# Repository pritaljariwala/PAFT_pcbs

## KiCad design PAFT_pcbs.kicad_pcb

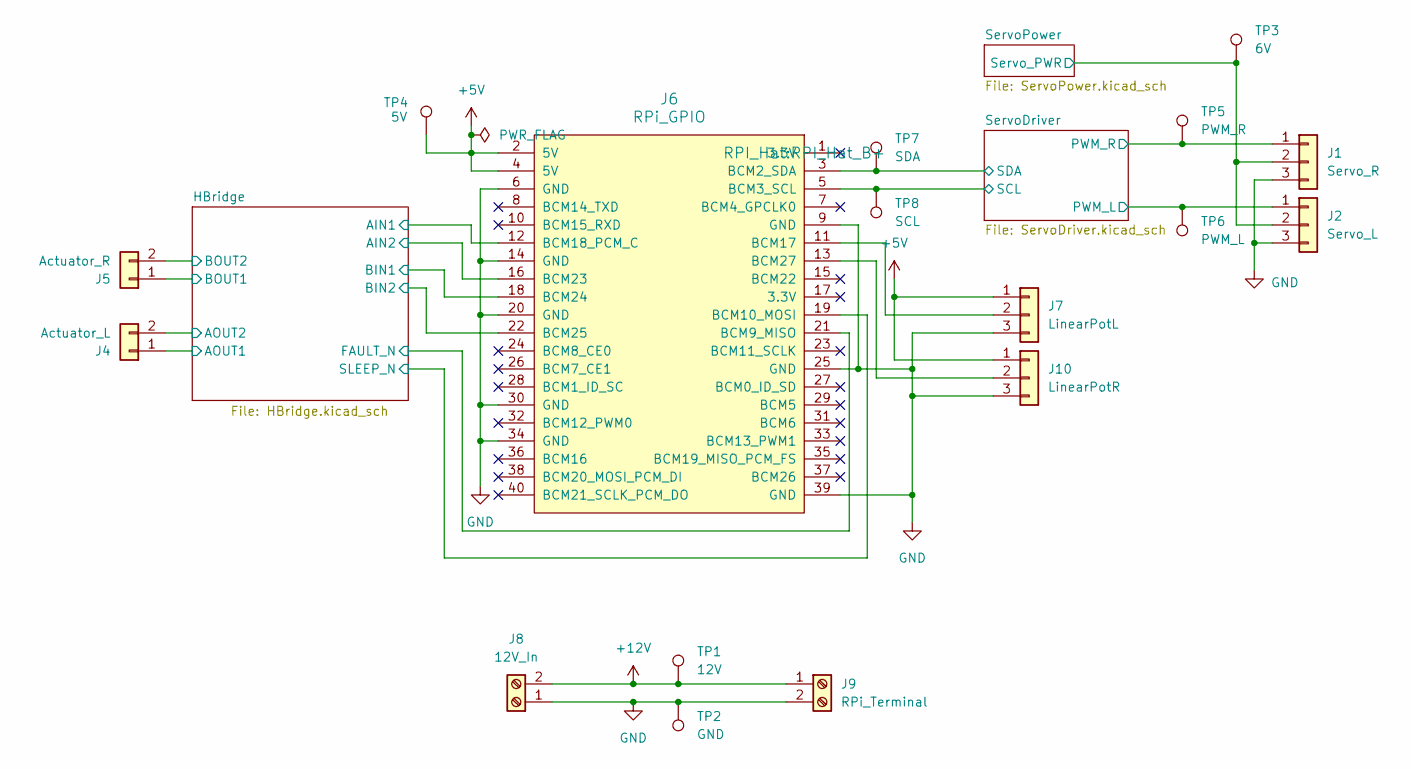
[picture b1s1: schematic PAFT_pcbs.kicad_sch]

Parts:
J1: Servo_R; PinHeader_1x03_P2.00mm_Vertical
J2: Servo_L; PinHeader_1x03_P2.00mm_Vertical
J4: Actuator_L; PinHeader_1x02_P2.00mm_Vertical
J5: Actuator_R; PinHeader_1x02_P2.00mm_Vertical
J6: RPi_GPIO; RPI_Hat_B+
J7: LinearPotL; PinHeader_1x03_P2.00mm_Vertical
J8: 12V_In; TerminalBlock_MaiXu_MX126-5.0-02P_1x02_P5.00mm
J9: RPi_Terminal; TerminalBlock_MaiXu_MX126-5.0-02P_1x02_P5.00mm
J10: LinearPotR; PinHeader_1x03_P2.00mm_Vertical
TP1: 12V; TestPoint_Plated_Hole_D2.0mm
TP2: GND; TestPoint_Plated_Hole_D2.0mm
TP3: 6V; TestPoint_Plated_Hole_D2.0mm
TP4: 5V; TestPoint_Plated_Hole_D2.0mm
TP5: PWM_R; TestPoint_Plated_Hole_D2.0mm
TP6: PWM_L; TestPoint_Plated_Hole_D2.0mm
TP7: SDA; TestPoint_Plated_Hole_D2.0mm
TP8: SCL; TestPoint_Plated_Hole_D2.0mm

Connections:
+5V: J6.2 (5V), J6.4 (5V), J7.1, J10.1, TP4.1; also elsewhere on the board
+12V: J8.2, J9.1, TP1.1; also elsewhere on the board
/HBridge/AIN1: J6.12 (BCM18_PCM_C); also elsewhere on the board
/HBridge/AIN2: J6.16 (BCM23); also elsewhere on the board
/HBridge/AOUT1: J4.1; also elsewhere on the board
/HBridge/AOUT2: J4.2; also elsewhere on the board
/HBridge/BIN1: J6.18 (BCM24); also elsewhere on the board
/HBridge/BIN2: J6.22 (BCM25); also elsewhere on the board
/HBridge/BOUT1: J5.1; also elsewhere on the board
/HBridge/BOUT2: J5.2; also elsewhere on the board
/HBridge/FAULT_N: J6.21 (BCM9_MISO); also elsewhere on the board
/HBridge/SLEEP_N: J6.19 (BCM10_MOSI); also elsewhere on the board
/ServoDriver/PWM_L: J2.1, TP6.1; also elsewhere on the board
/ServoDriver/PWM_R: J1.1, TP5.1; also elsewhere on the board
/ServoDriver/SCL: J6.5 (BCM3_SCL), TP8.1; also elsewhere on the board
/ServoDriver/SDA: J6.3 (BCM2_SDA), TP7.1; also elsewhere on the board
/ServoPower/Servo_PWR: J1.2, J2.2, TP3.1; also elsewhere on the board
GND: J1.3, J2.3, J6.6 (GND), J6.9 (GND), J6.14 (GND), J6.20 (GND), J6.25 (GND), J6.30 (GND), J6.34 (GND), J6.39 (GND), J7.3, J8.1, J9.2, J10.3, TP2.1; also elsewhere on the board
unnamed: J6.11 (BCM17), J7.2
unnamed: J6.13 (BCM27), J10.2

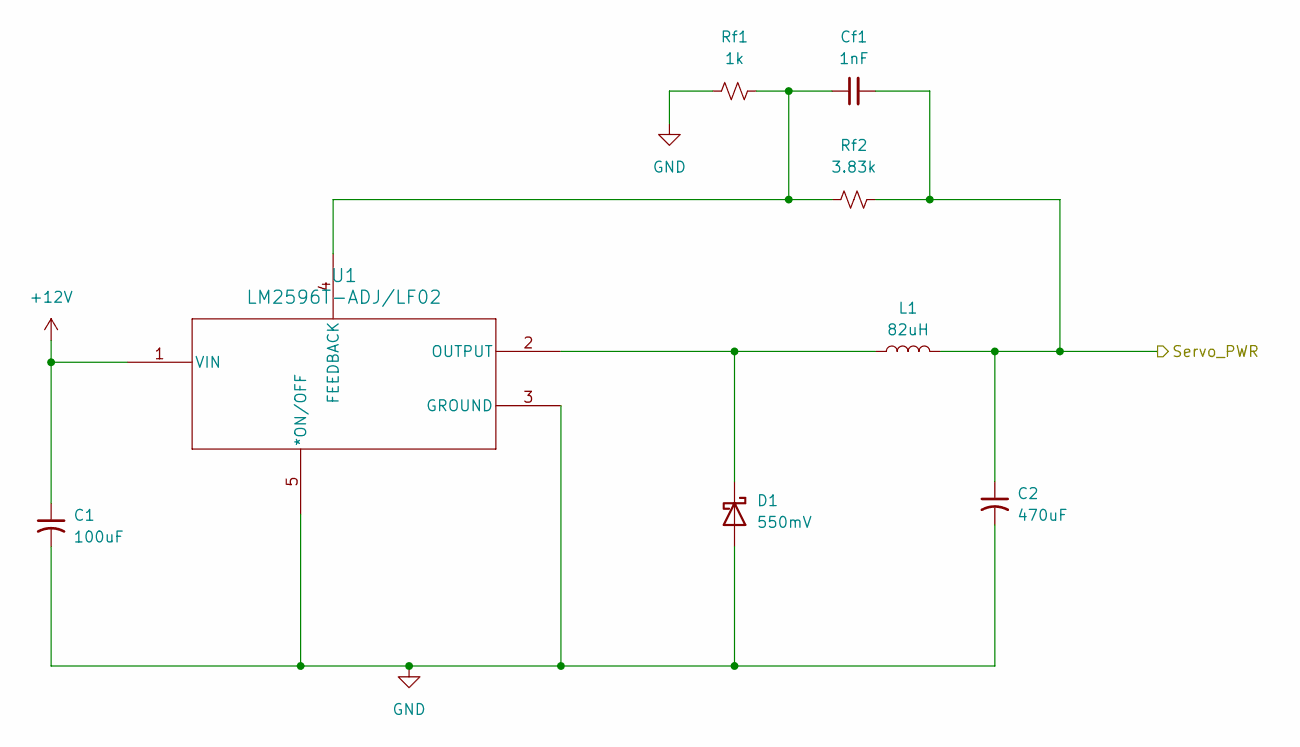
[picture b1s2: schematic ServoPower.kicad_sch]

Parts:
C1: 100uF; C_Elec_6.3x5.4
C2: 470uF; C_Elec_10x10.2
Cf1: 1nF; C_0603_1608Metric
D1: 550mV; D_3220_8050Metric
L1: 82uH; L_Bourns_SRR1260
Rf1: 1k; R_0805_2012Metric
Rf2: 3.83k; R_0805_2012Metric
U1: LM2596T-ADJ/LF02; TO170P470X1016X2092-5P

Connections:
+12V: C1.1, U1.1 (VIN); also elsewhere on the board
/ServoPower/Servo_PWR: C2.1, Cf1.2, L1.2, Rf2.2; also elsewhere on the board
GND: C1.2, C2.2, D1.2 (A), Rf1.2, U1.3 (GROUND), U1.5 (*ON/OFF); also elsewhere on the board
unnamed: D1.1 (K), L1.1, U1.2 (OUTPUT)
unnamed: Cf1.1, Rf1.1, Rf2.1, U1.4 (FEEDBACK)

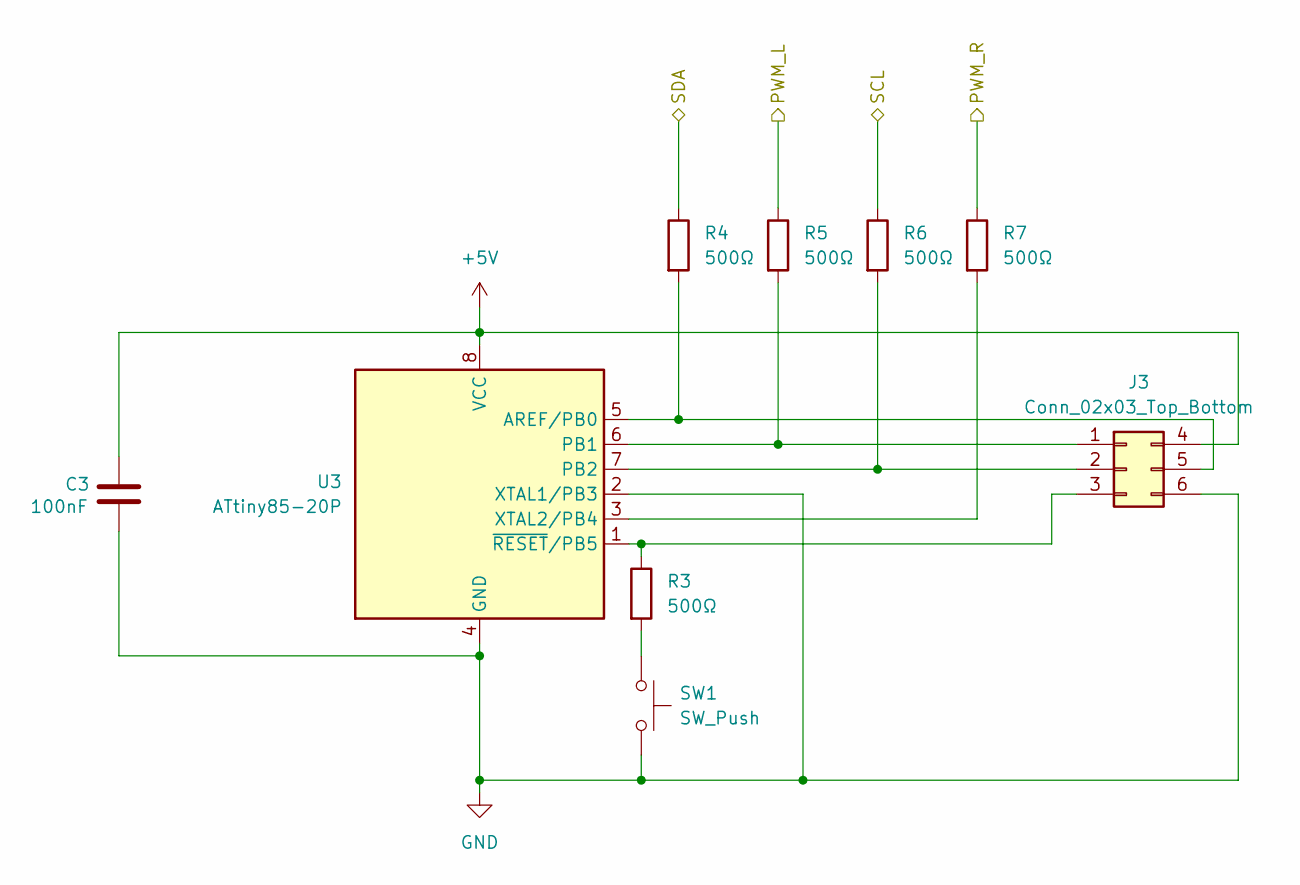
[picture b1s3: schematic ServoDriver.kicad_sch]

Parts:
C3: 100nF; C_0805_2012Metric
J3: Conn_02x03_Top_Bottom; PinHeader_2x03_P2.54mm_Vertical
R3, R4, R5, R6, R7: 500Ω; R_0805_2012Metric
SW1: SW_Push; SW_PUSH_6mm_H4.3mm
U3: ATtiny85-20P; DIP-8_W7.62mm

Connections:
+5V: C3.1, J3.4, U3.8 (VCC); also elsewhere on the board
/ServoDriver/PWM_L: R5.1; also elsewhere on the board
/ServoDriver/PWM_R: R7.1; also elsewhere on the board
/ServoDriver/SCL: R6.1; also elsewhere on the board
/ServoDriver/SDA: R4.1; also elsewhere on the board
GND: C3.2, J3.6, SW1.2, U3.2 (XTAL1/PB3), U3.4 (GND); also elsewhere on the board
unnamed: J3.1, R5.2, U3.6 (PB1)
unnamed: J3.2, R6.2, U3.7 (PB2)
unnamed: J3.3, R3.1, U3.1 (~RESET/PB5)
unnamed: J3.5, R4.2, U3.5 (AREF/PB0)
unnamed: R3.2, SW1.1
unnamed: R7.2, U3.3 (XTAL2/PB4)

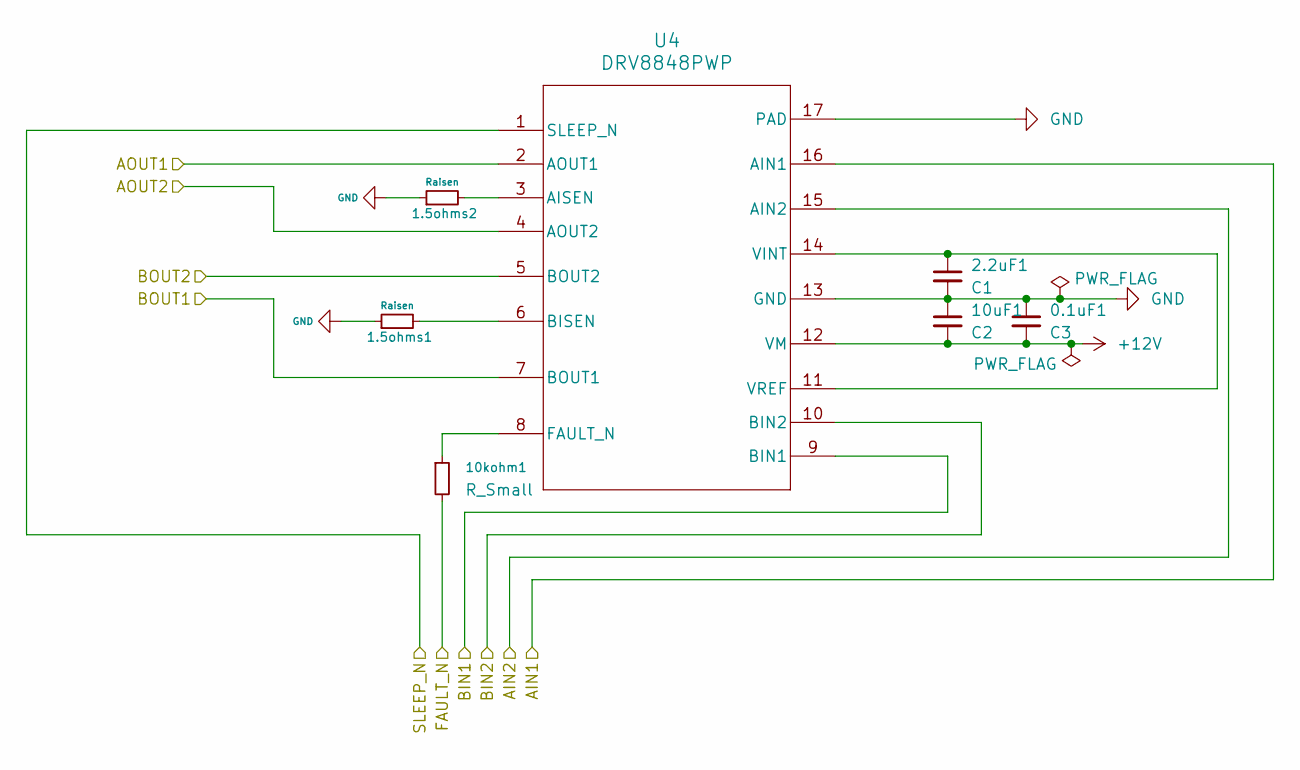
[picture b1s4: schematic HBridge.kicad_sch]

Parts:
0.1uF1: C3; C_0805_2012Metric
1.5ohms1, 1.5ohms2: Raisen; R_1210_3225Metric
2.2uF1: C1; C_1210_3225Metric
10kohm1: R_Small; R_0805_2012Metric
10uF1: C2; C_1206_3216Metric
U4: DRV8848PWP; IC_DRV8848PWP

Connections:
+12V: 0.1uF1.2, 10uF1.2, U4.12 (VM); also elsewhere on the board
/HBridge/AIN1: U4.16 (AIN1); also elsewhere on the board
/HBridge/AIN2: U4.15 (AIN2); also elsewhere on the board
/HBridge/AOUT1: U4.2 (AOUT1); also elsewhere on the board
/HBridge/AOUT2: U4.4 (AOUT2); also elsewhere on the board
/HBridge/BIN1: U4.9 (BIN1); also elsewhere on the board
/HBridge/BIN2: U4.10 (BIN2); also elsewhere on the board
/HBridge/BOUT1: U4.7 (BOUT1); also elsewhere on the board
/HBridge/BOUT2: U4.5 (BOUT2); also elsewhere on the board
/HBridge/FAULT_N: 10kohm1.2; also elsewhere on the board
/HBridge/SLEEP_N: U4.1 (SLEEP_N); also elsewhere on the board
GND: 0.1uF1.1, 1.5ohms1.1, 1.5ohms2.1, 2.2uF1.2, 10uF1.1, U4.13 (GND), U4.17 (PAD), U4.18, U4.19, U4.20, U4.21, U4.22, U4.23, U4.24, U4.25, U4.26, U4.27, U4.28, U4.29; also elsewhere on the board
unnamed: 1.5ohms2.2, U4.3 (AISEN)
unnamed: 1.5ohms1.2, U4.6 (BISEN)
unnamed: 10kohm1.1, U4.8 (FAULT_N)
unnamed: 2.2uF1.1, U4.11 (VREF), U4.14 (VINT)

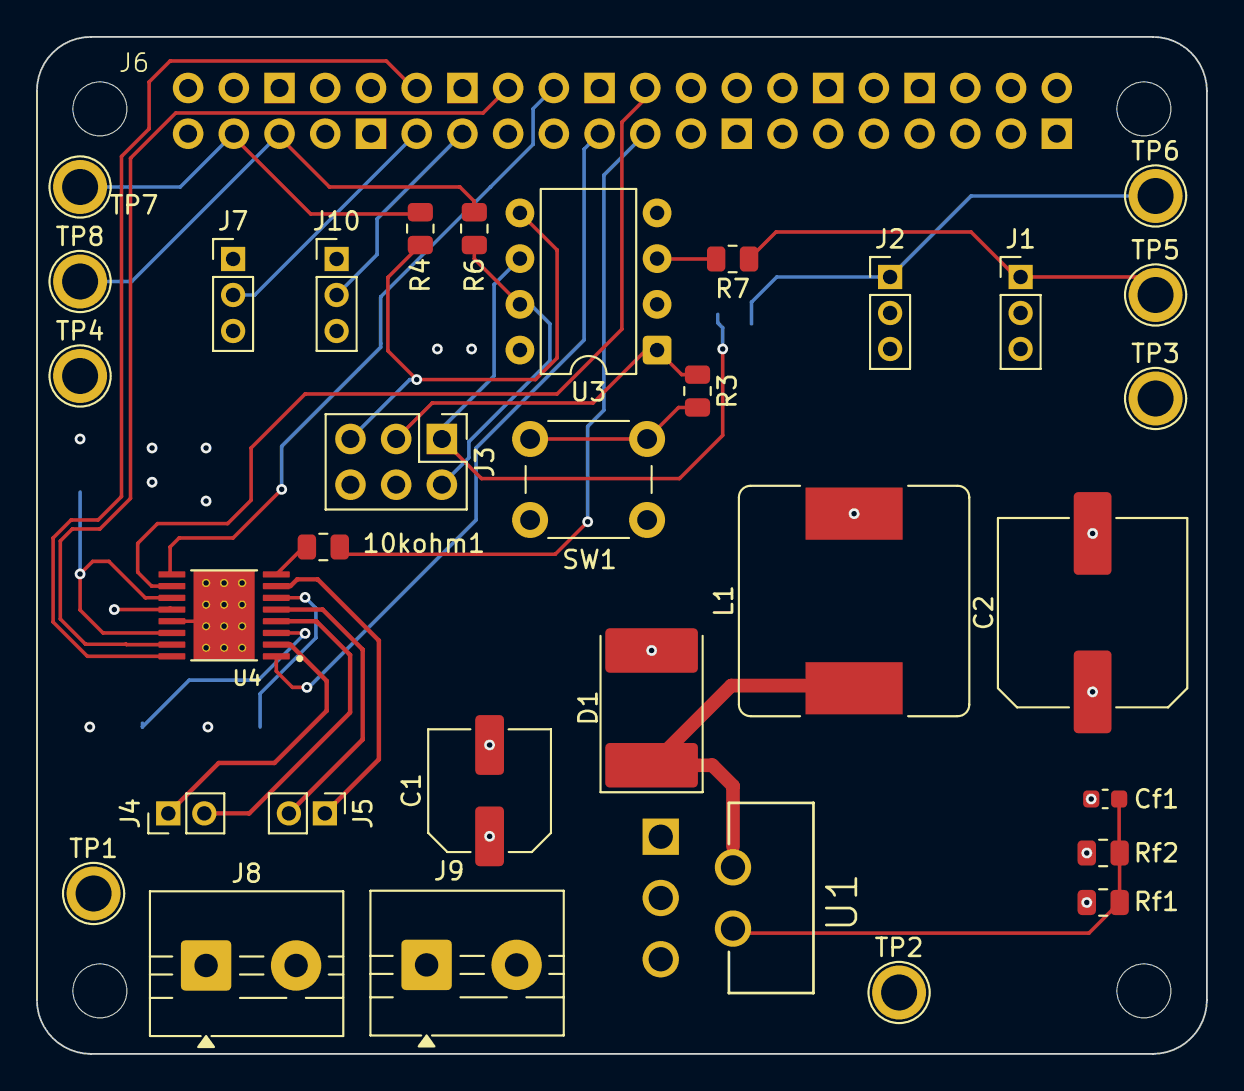
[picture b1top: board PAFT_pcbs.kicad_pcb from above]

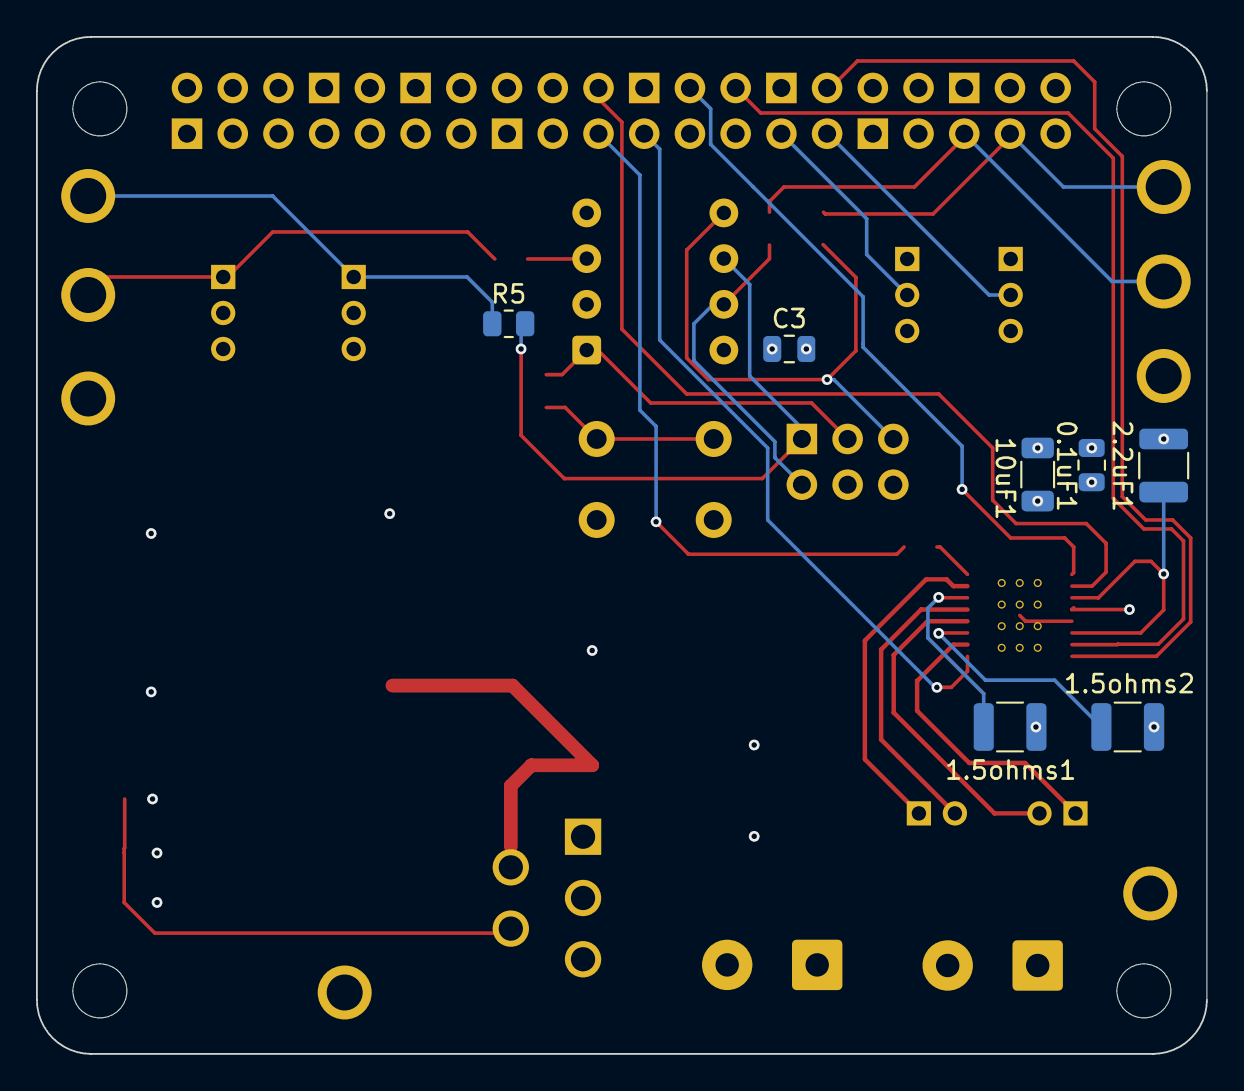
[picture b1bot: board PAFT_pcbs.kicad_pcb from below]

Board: 4 copper layers, 65.0 x 56.5 mm, 41 parts (7 on the bottom side), 32 nets.

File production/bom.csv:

Designator,Footprint,Quantity,Value,LCSC Part #
0.1UF1,0805,1,C3,
"1.5OHMS1, 1.5OHMS2",1210,2,Raisen,
10KOHM1,0805,1,R_Small,
10UF1,1206,1,C2,
2.2UF1,1210,1,C1,
C1,C_Elec_6.3x5.4,1,100uF,
C2,C_Elec_10x10.2,1,470uF,
C3,0805,1,100nF,
CF1,0603,1,1nF,
D1,3220,1,550mV,
J1,PinHeader_1x03_P2.00mm_Vertical,1,Servo_R,
J10,PinHeader_1x03_P2.00mm_Vertical,1,LinearPotR,
J2,PinHeader_1x03_P2.00mm_Vertical,1,Servo_L,
J3,PinHeader_2x03_P2.54mm_Vertical,1,Conn_02x03_Top_Bottom,
J4,PinHeader_1x02_P2.00mm_Vertical,1,Actuator_L,
J5,PinHeader_1x02_P2.00mm_Vertical,1,Actuator_R,
J6,RPI_Hat_B+,1,RPi_GPIO,
J7,PinHeader_1x03_P2.00mm_Vertical,1,LinearPotL,
J8,TerminalBlock_MaiXu_MX126-5.0-02P_1x02_P5.00mm,1,12V_In,
J9,TerminalBlock_MaiXu_MX126-5.0-02P_1x02_P5.00mm,1,RPi_Terminal,
L1,L_Bourns_SRR1260,1,82uH,
"R3, R4, R5, R6, R7",0805,5,500Ω,
RF1,0805,1,1k,
RF2,0805,1,3.83k,
SW1,SW_PUSH_6mm_H4.3mm,1,SW_Push,
TP1,TestPoint_Plated_Hole_D2.0mm,1,12V,
TP2,TestPoint_Plated_Hole_D2.0mm,1,GND,
TP3,TestPoint_Plated_Hole_D2.0mm,1,6V,
TP4,TestPoint_Plated_Hole_D2.0mm,1,5V,
TP5,TestPoint_Plated_Hole_D2.0mm,1,PWM_R,
TP6,TestPoint_Plated_Hole_D2.0mm,1,PWM_L,
TP7,TestPoint_Plated_Hole_D2.0mm,1,SDA,
TP8,TestPoint_Plated_Hole_D2.0mm,1,SCL,
U1,TO170P470X1016X2092-5P,1,LM2596T-ADJ/LF02,
U3,DIP-8_W7.62mm,1,ATtiny85-20P,
U4,IC_DRV8848PWP,1,DRV8848PWP,

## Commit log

2026-02-03 removed old untagged folder
2026-02-10 added DRV8848
2026-02-24 add new sheets
2026-03-02 ServoDriver schematic
2026-03-03 HBridge stuff
2026-03-03 HBridge top file connections (NOT CONNECTED TO TOP FILE YET)
2026-03-03 Fixed Merge Conflicts
2026-03-03 Revert "Fixed Merge Conflicts"
    This reverts commit 1dcac9fe20d43ad9866d81964f948f071540213e.
2026-03-03 blah
2026-03-03 Servo Power added to child
2026-03-03 Added HBridge pins to top schematic
2026-03-04 Added voltage/signal test points
2026-03-04 USB C IC added
2026-03-10 Updated schematic
2026-03-10 Added footprints
2026-03-13 ICs added
2026-03-13 forgot to close out kicad before pushing lol
2026-03-14 PCB Placement and Planes
2026-03-15 PCB traces routed
2026-03-24 errors resolved
2026-03-26 Routing adjustments
2026-03-27 Fixed DRC errors
2026-03-27 Routing updates
2026-03-27 Final updates
2026-03-30 Production edits
